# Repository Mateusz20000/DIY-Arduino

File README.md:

# DIY-Arduino
Files and schematics for creating DIY Arduino

This project contains files for creating your own Arduino platform.
It's completely open source.

Arduino is free, open source platform that helps you understeand basics of electronics.

Electrical scheme:

<br>

PCB scheme:

<br>

3D Render:

<br>

Phisical result:
<h1 style={color: red;}>NOT MADE YET, PLEASE FOLLOW FOR UPDATE</h1>

<br>

Hope that this is helpful for you :)

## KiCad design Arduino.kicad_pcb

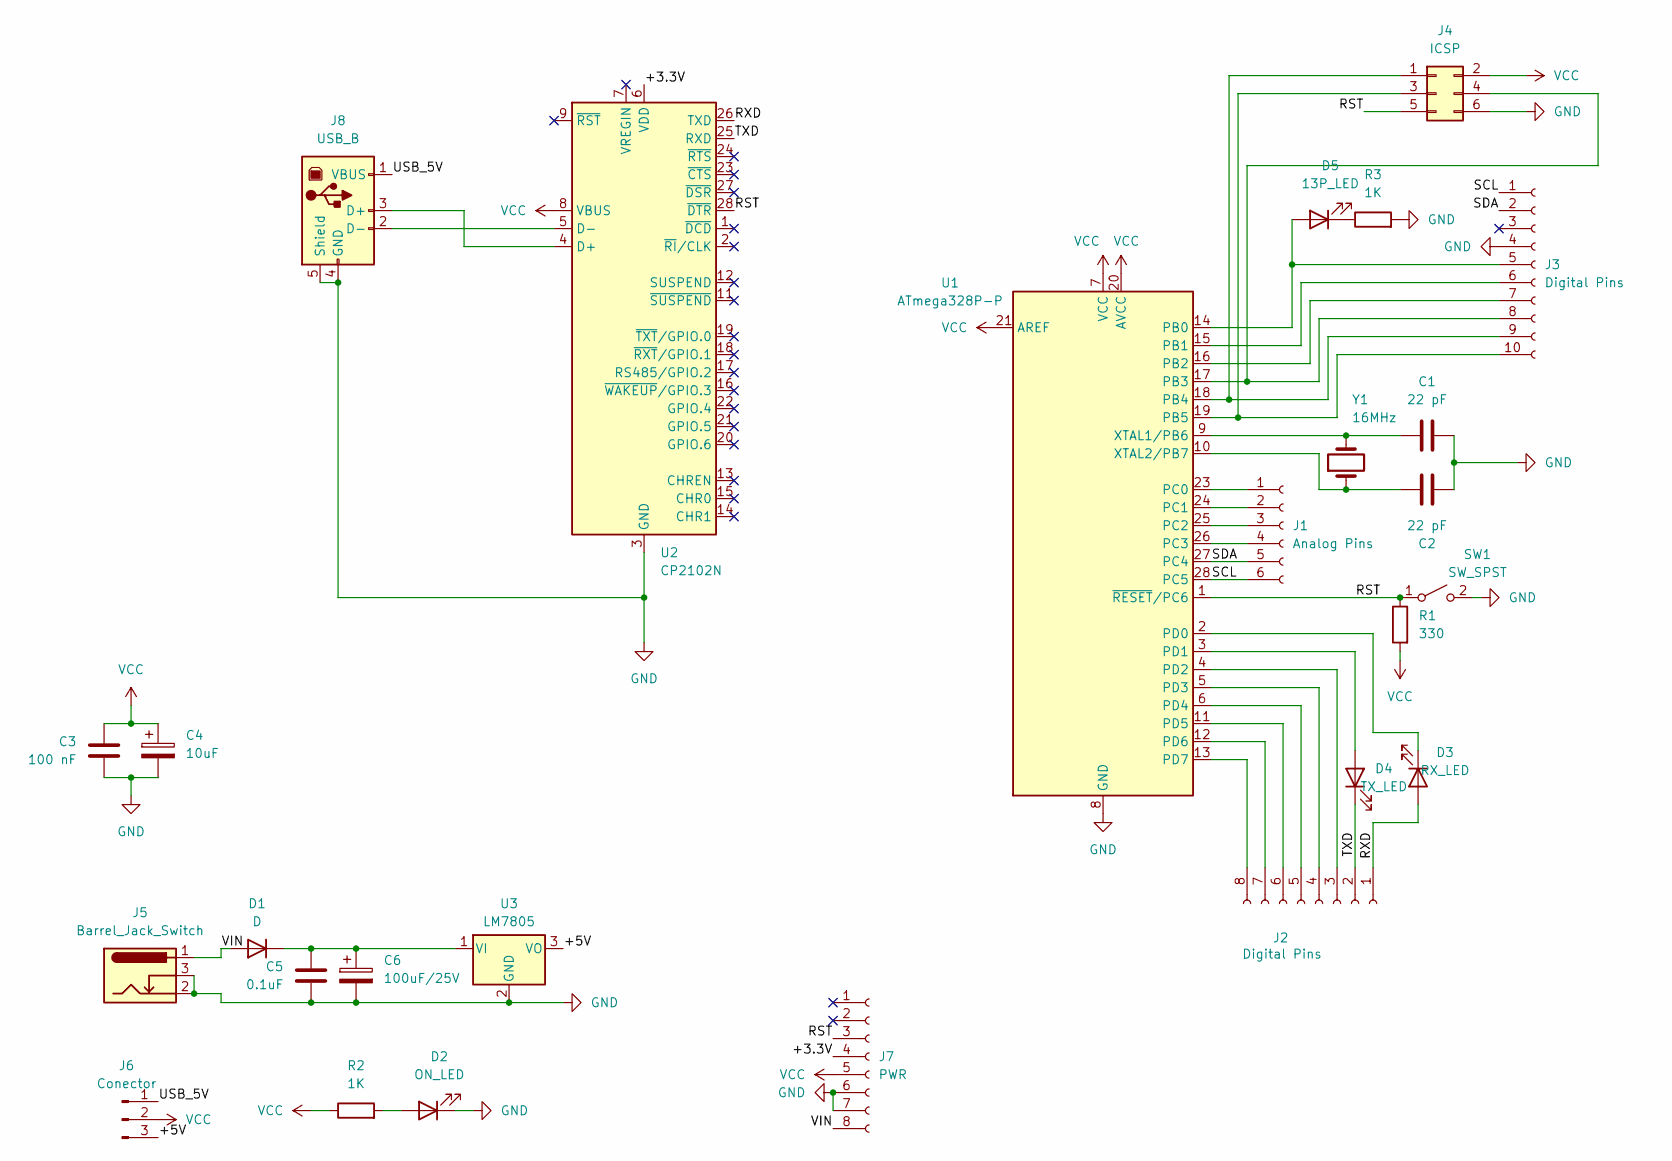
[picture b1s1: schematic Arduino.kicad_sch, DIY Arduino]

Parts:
C1, C2: 22 pF; C_Disc_D4.7mm_W2.5mm_P5.00mm
C3: 100 nF; Capacitor Pad
C4: 10uF; Capacitor Pad
C5: 0.1uF; Capacitor Pad
C6: 100uF/25V; Capacitor Pad
D1: D; 2 Pad
D2: ON_LED; LED_D3.0mm
D3: RX_LED; LED_D3.0mm
D4: TX_LED; LED_D3.0mm
D5: 13P_LED; LED_D3.0mm
J1: Analog Pins; 6 Pin Connector
J2: Digital Pins; 8 Pin Connector
J3: Digital Pins; 10 Pin Connector
J4: ICSP; 2x3 Pin Connector
J5: Barrel_Jack_Switch; BarrelJack_Horizontal
J6: Conector; 3 Pin Connector
J7: PWR; 8 Pin Connector
J8: USB_B; USB_B_OST_USB-B1HSxx_Horizontal
R1: 330; 2 Pad
R2, R3: 1K; 2 Pad
SW1: SW_SPST; Button Pad
U1: ATmega328P-P; DIP-28_W7.62mm
U2: CP2102N; QFN-28-1EP_5x5mm_P0.5mm_EP3.35x3.35mm
U3: LM7805; TO-220-3_Vertical
Y1: 16MHz; Oscillator Pad

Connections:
/+3.3V: J7.4, U2.6 (VDD)
/+5V: J6.3, U3.3 (VO)
/RST: J4.5, J7.3, R1.1, SW1.1 (A), U1.1 (~RESET/PC6), U2.28 (~DTR)
/RXD: D3.2 (A), J2.1, U2.26 (TXD)
/SCL: J1.6, J3.1, U1.28 (PC5)
/SDA: J1.5, J3.2, U1.27 (PC4)
/TXD: D4.1 (K), J2.2, U2.25 (RXD)
/USB_5V: J6.1, J8.1 (VBUS)
/VIN: D1.2 (A), J5.1, J7.8
GND: C1.2, C2.2, C3.2, C4.2, C5.2, C6.2, D2.1 (K), J3.4, J4.6, J5.2, J5.3, J7.6, J7.7, J8.4 (GND), J8.5 (Shield), R3.2, SW1.2 (B), U1.8 (GND), U1.22 (GND), U2.3 (GND), U2.29 (GND), U3.2 (GND)
unnamed: C5.1, C6.1, D1.1 (K), U3.1 (VI)
unnamed: D2.2 (A), R2.2
unnamed: D3.1 (K), U1.2 (PD0)
unnamed: D4.2 (A), U1.3 (PD1)
unnamed: D5.2 (A), J3.5, U1.14 (PB0)
unnamed: D5.1 (K), R3.1
unnamed: J1.1, U1.23 (PC0)
unnamed: J1.2, U1.24 (PC1)
unnamed: J1.3, U1.25 (PC2)
unnamed: J1.4, U1.26 (PC3)
unnamed: J2.3, U1.4 (PD2)
unnamed: J2.4, U1.5 (PD3)
unnamed: J2.5, U1.6 (PD4)
unnamed: J2.6, U1.11 (PD5)
unnamed: J2.7, U1.12 (PD6)
unnamed: J2.8, U1.13 (PD7)
unnamed: J3.6, U1.15 (PB1)
unnamed: J3.7, U1.16 (PB2)
unnamed: J3.8, J4.4, U1.17 (PB3)
unnamed: J3.9, J4.1, U1.18 (PB4)
unnamed: J3.10, J4.3, U1.19 (PB5)
unnamed: J8.3 (D+), U2.4 (D+)
unnamed: J8.2 (D-), U2.5 (D-)
unnamed: C1.1, U1.9 (XTAL1/PB6), Y1.2
unnamed: C2.1, U1.10 (XTAL2/PB7), Y1.1
VCC: C3.1, C4.1, J4.2, J6.2, J7.5, R1.2, R2.1, U1.7 (VCC), U1.20 (AVCC), U1.21 (AREF), U2.8 (VBUS)

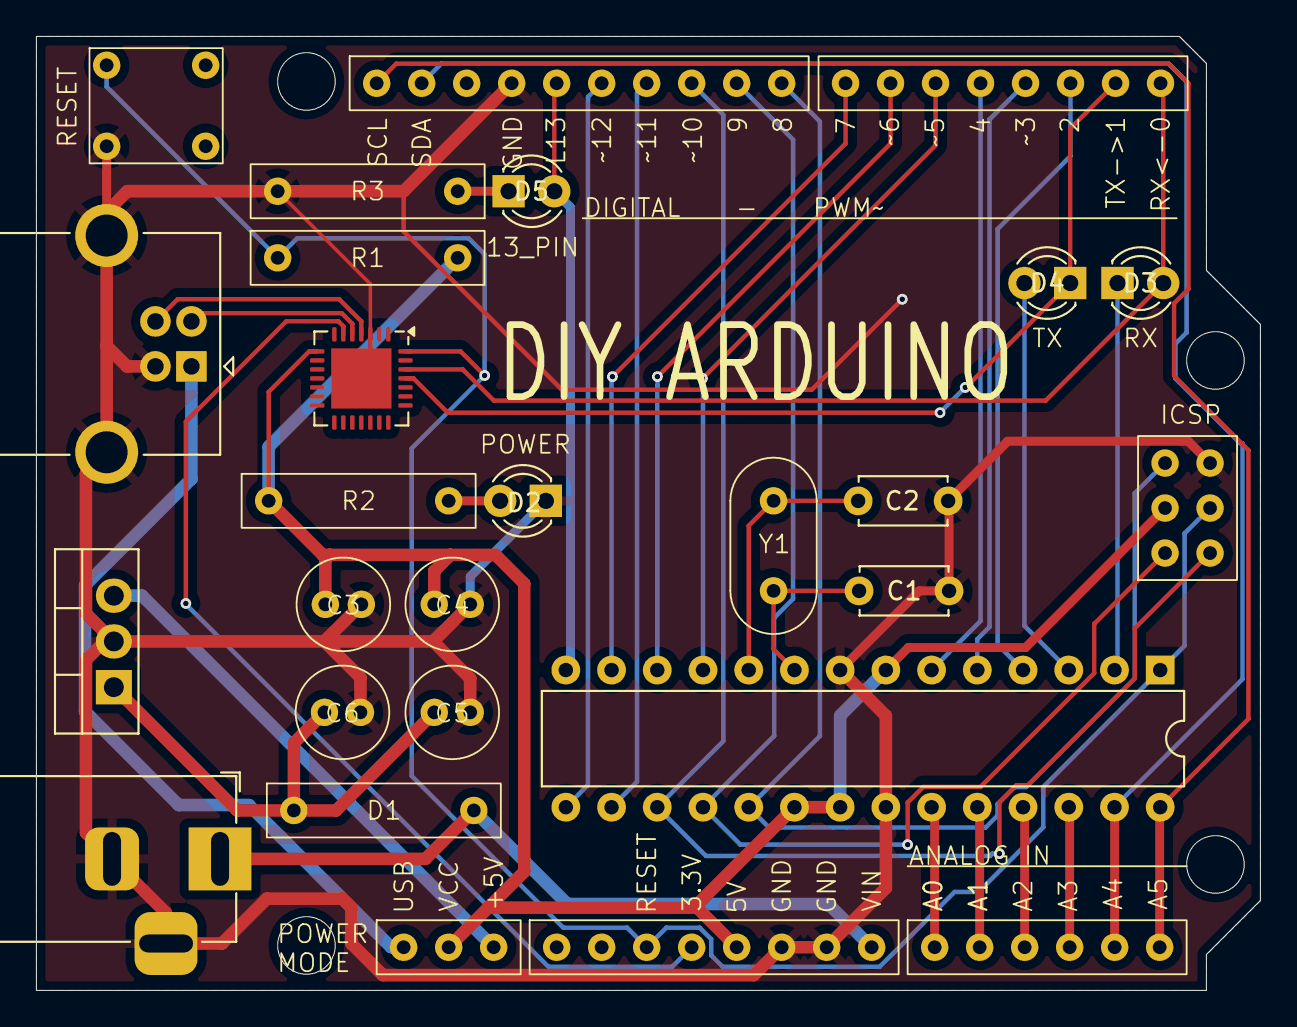
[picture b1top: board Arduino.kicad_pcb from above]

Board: 2 copper layers, 68.0 x 53.0 mm, 27 parts (0 on the bottom side), 36 nets.

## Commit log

2025-08-14 Finished Schematic for DIY Arduino
2025-08-14 Adding final version
2025-08-14 Added Gerber files
2025-08-14 Fixed small mistake
